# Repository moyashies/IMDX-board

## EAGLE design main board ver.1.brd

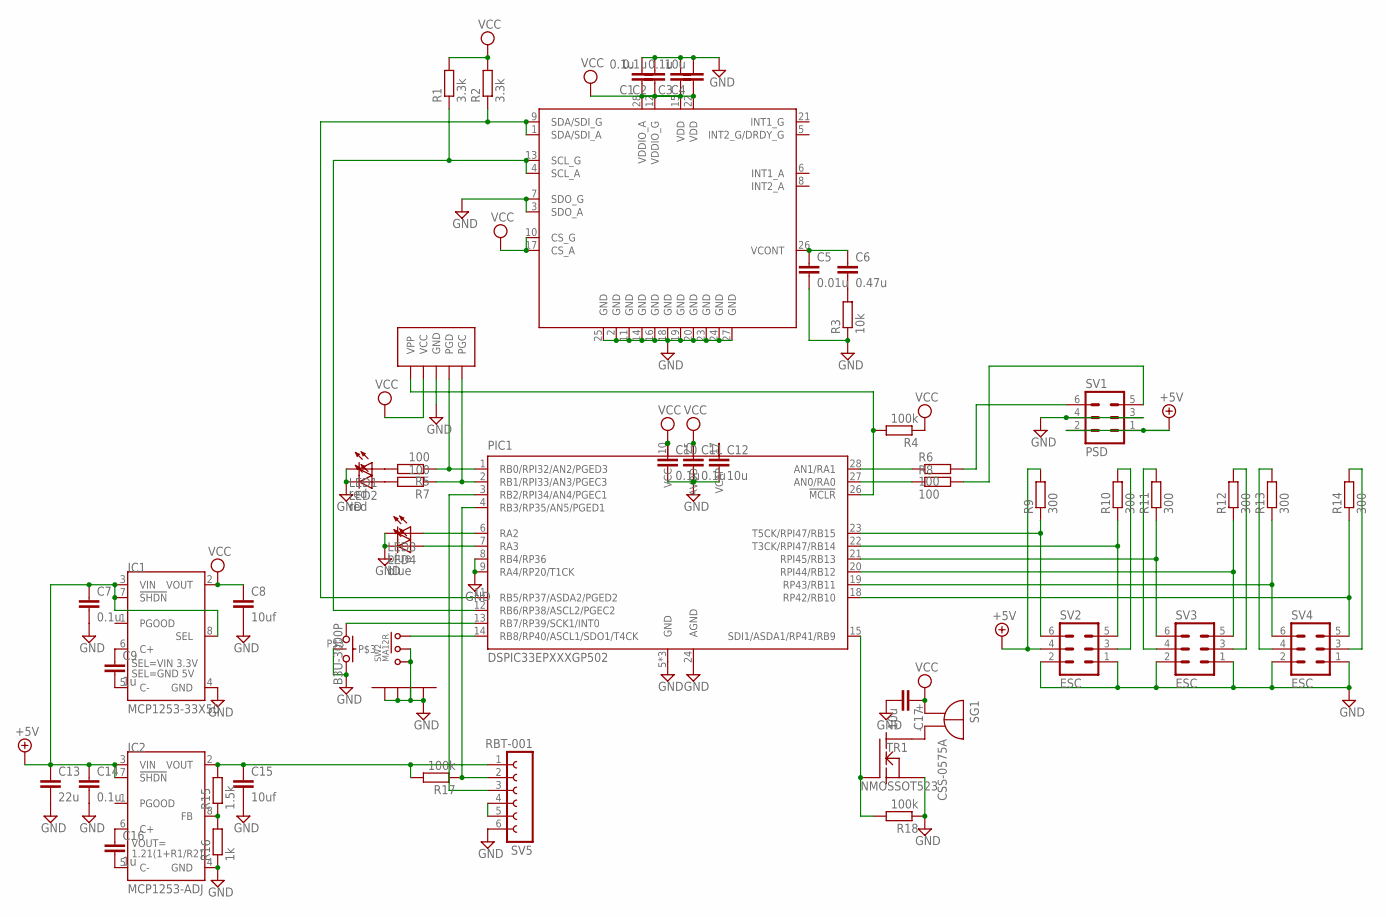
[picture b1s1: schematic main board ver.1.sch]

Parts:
C1, C2, C3, C7, C10, C11, C14: 0.1u; C0402-SS
C4, C12, C17: 10u; C0805
C5: 0.01u; C0402-SS
C6: 0.47u; C0402-SS
C8, C15: 10uf; C0805
C9, C16: 1u; C0603
C13: 22u; C1206
IC1: MCP1253-33X50; MSOP8
IC2: MCP1253-ADJ; MSOP8
IMU1: LSM330DLRM; LLGA28L(RM)
LED1, LED2: red; CHIP-LED1005
LED3, LED4: blue; CHIP-LED1005
PIC1: DSPIC33EPXXXGP502; QFN28-ML_6X6MM
R1, R2: 3.3k; R0402-SS
R3: 10k; R0402-SS
R4, R17, R18: 100k; R0402-SS
R5, R6, R7, R8: 100; R0402-SS
R9, R10, R11, R12, R13, R14: 300; R0402-SS
R15: 1.5k; R0402-SS
R16: 1k; R0402-SS
SG1: CSS-0575A
SV1: PSD; MA03-2
SV2, SV3, SV4: ESC; MA03-2
SV5: RBT-001; NPPN061BFLC
SW1: B3U-3000P
SW2: MA12R
TR1: NMOSSOT523; SOT523
U$1: ICSP; MINI-ICSP

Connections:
+5V: C7.1, C13.1, C14.1, IC1.3 (VIN), IC1.7 (!SHDN!), IC1.8 (SEL), IC2.3 (VIN), IC2.7 (!SHDN!), R9.2, SV1.1, SV1.2, SV2.4
GND: C1.2, C2.2, C3.2, C4.2, C5.2, C7.2, C8.2, C10.2, C11.2, C12.2, C13.2, C14.2, C15.2, C17.2, IC1.4 (GND), IC2.4 (GND), IMU1.2 (GND), IMU1.3 (SDO_A), IMU1.7 (SDO_G), IMU1.11 (GND), IMU1.14 (GND), IMU1.16 (GND), IMU1.18 (GND), IMU1.19 (GND), IMU1.20 (GND), IMU1.23 (GND), IMU1.24 (GND), IMU1.25 (GND), IMU1.27 (GND), LED1.C, LED2.C, LED3.C, LED4.C, PIC1.5 (GND), PIC1.8 (RB4/RP36), PIC1.9 (RA4/RP20/T1CK), PIC1.16 (GND), PIC1.24 (AGND), PIC1.EXP (GND), R3.1, R16.1, R18.1, SV1.3, SV1.4, SV2.1, SV2.2, SV3.1, SV3.2, SV4.1, SV4.2, SV5.6, SW1.P$2, SW1.P$3, SW2.P$2 (2), SW2.P$3 (3), SW2.P$4, SW2.P$5, SW2.P$6, SW2.P$7, TR1.2 (S), U$1.GND
unnamed: C16.1, IC2.6 (C+)
unnamed: C16.2, IC2.5 (C-)
unnamed: PIC1.28 (AN1/RA1), R6.1
unnamed: PIC1.27 (AN0/RA0), R8.1
unnamed: C15.1, IC2.2 (VOUT), R15.2, R17.2, SV5.1
unnamed: IC2.8 (FB), R15.1, R16.2
unnamed: R8.2, SV1.5
unnamed: C12.1, PIC1.17 (VCAP)
unnamed: PIC1.18 (RP42/RB10), R14.1, SV4.5
unnamed: C5.1, C6.1, IMU1.26 (VCONT)
unnamed: C6.2, R3.2
unnamed: PIC1.19 (RP43/RB11), R13.1, SV4.6
unnamed: PIC1.20 (RPI44/RB12), R12.1, SV3.5
unnamed: IMU1.1 (SDA/SDI_A), IMU1.9 (SDA/SDI_G), PIC1.11 (RB5/RP37/ASDA2/PGED2), R2.1
unnamed: SG1.-, TR1.3 (D)
unnamed: LED4.A, PIC1.7 (RA3)
unnamed: PIC1.21 (RPI45/RB13), R11.1, SV3.6
unnamed: PIC1.22 (T3CK/RPI47/RB14), R10.1, SV2.5
unnamed: PIC1.23 (T5CK/RPI47/RB15), R9.1, SV2.6
unnamed: IMU1.4 (SCL_A), IMU1.13 (SCL_G), PIC1.12 (RB6/RP38/ASCL2/PGEC2), R1.1
unnamed: PIC1.15 (SDI1/ASDA1/RP41/RB9), R18.2, TR1.1 (G)
unnamed: LED3.A, PIC1.6 (RA2)
unnamed: LED1.A, R5.2
unnamed: PIC1.1 (RB0/RPI32/AN2/PGED3), R5.1, U$1.PGD
unnamed: PIC1.2 (RB1/RPI33/AN3/PGEC3), R7.1, U$1.PGC
unnamed: PIC1.3 (RB2/RPI34/AN4/PGEC1), SV5.3
unnamed: PIC1.4 (RB3/RP35/AN5/PGED1), R17.1, SV5.2
unnamed: LED2.A, R7.2
unnamed: PIC1.14 (RB8/RP40/ASCL1/SDO1/T4CK), SW2.P$1 (1)
unnamed: PIC1.13 (RB7/RP39/SCK1/INT0), SW1.P$1
unnamed: PIC1.26 (!MCLR!), R4.2, U$1.VPP
unnamed: R6.2, SV1.6
unnamed: SV5.4, SV5.5
unnamed: C9.1, IC1.6 (C+)
unnamed: C9.2, IC1.5 (C-)
unnamed: R10.2, SV2.3
unnamed: R11.2, SV3.4
unnamed: R12.2, SV3.3
unnamed: R13.2, SV4.4
unnamed: R14.2, SV4.3
VCC: C1.1, C2.1, C3.1, C4.1, C8.1, C10.1, C11.1, C17.1, IC1.2 (VOUT), IMU1.10 (CS_G), IMU1.12 (VDDIO_G), IMU1.15 (VDD), IMU1.17 (CS_A), IMU1.22 (VDD), IMU1.28 (VDDIO_A), PIC1.10 (VCC), PIC1.25 (AVDD), R1.2, R2.2, R4.1, SG1.+, U$1.VCC

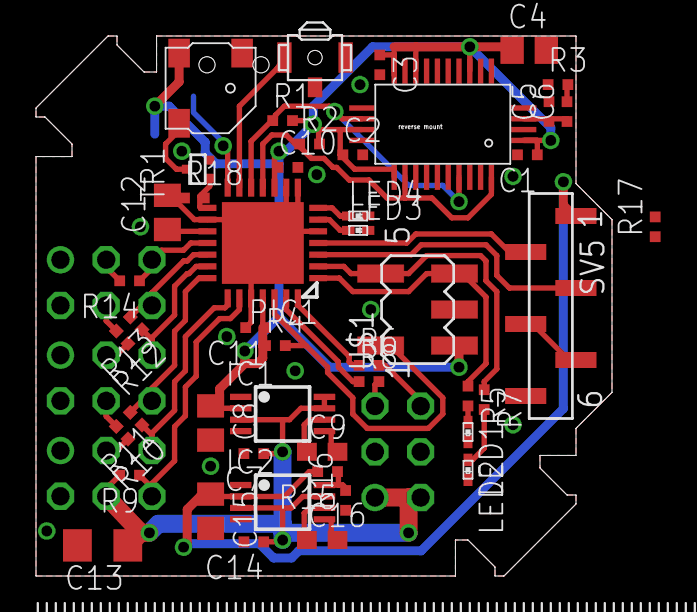
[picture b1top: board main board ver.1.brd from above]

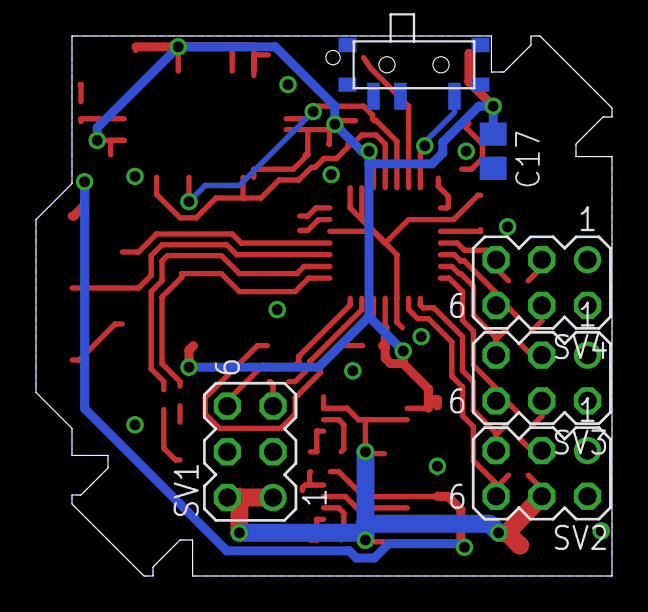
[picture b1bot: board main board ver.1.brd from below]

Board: 2 copper layers, 32.0 x 30.0 mm, 54 parts (6 on the bottom side), 43 nets.

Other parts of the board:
U$2: RULER-S

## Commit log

2013-03-11 initial import
